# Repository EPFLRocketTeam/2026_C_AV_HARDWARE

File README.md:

# 2026_C_AV_HARDWARE
Repository containing PCBs files of FH2 Avionics

## Guidelines
This repository should be used to share your hardware project files with other members of the team.
Add your project root folder to the indexing and create commits with tags to track versioning of your PCB as you make progress in the design.
Create a tagged release for each major version of your PCB that enters production.
As the repository holds all the AV boards CAD files, you should prefix the tag with the name of your subfolder project.
Take care to preserve tags and respective folders of other members.

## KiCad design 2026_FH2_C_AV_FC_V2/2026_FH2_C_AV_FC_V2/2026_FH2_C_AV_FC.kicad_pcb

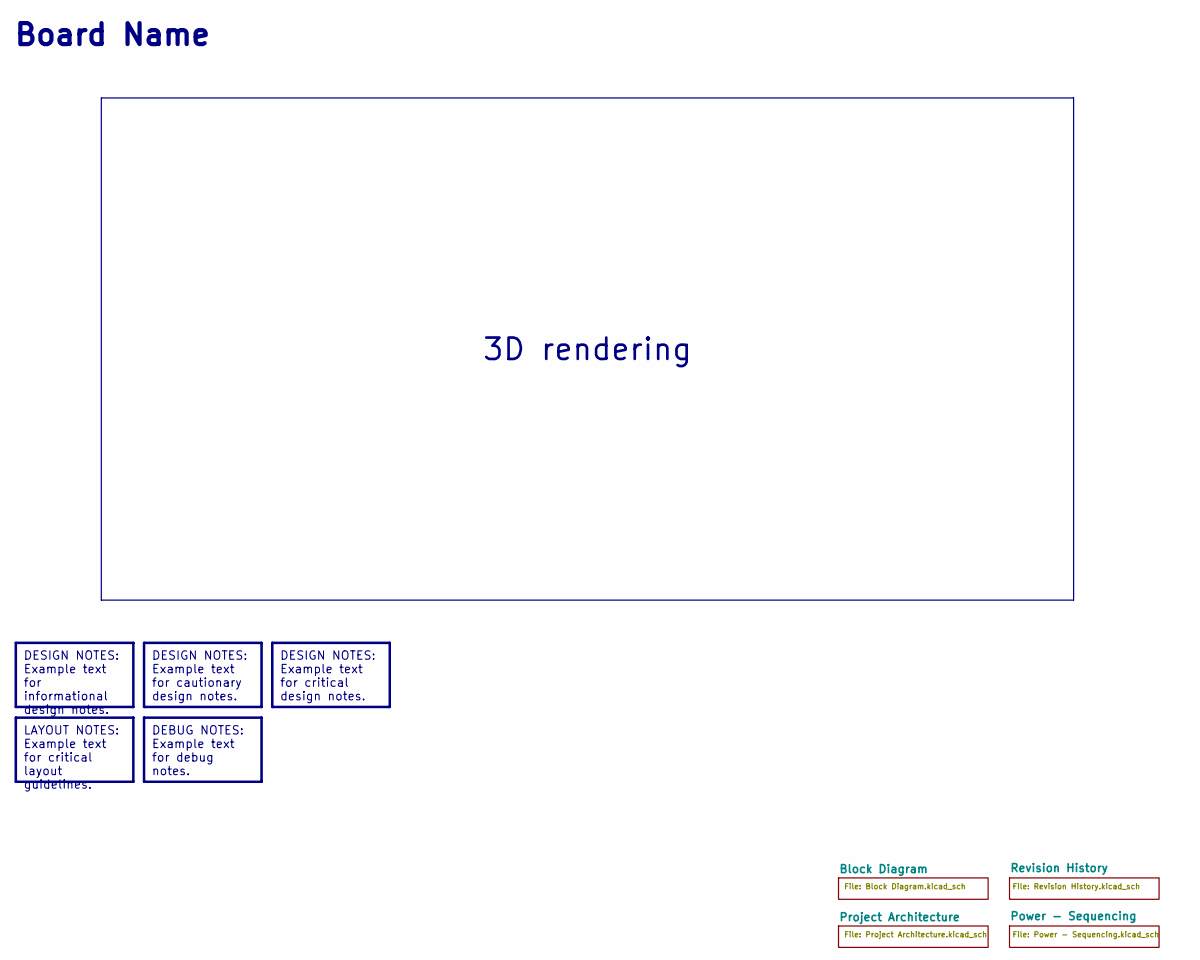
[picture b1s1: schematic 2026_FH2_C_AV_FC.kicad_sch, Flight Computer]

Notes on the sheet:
Board Name
DESIGN NOTES: Example text for informational design notes.
3D rendering
DESIGN NOTES: Example text for critical design notes.
DESIGN NOTES: Example text for cautionary design notes.
DEBUG NOTES: Example text for debug notes.
LAYOUT NOTES: Example text for critical layout guidelines.

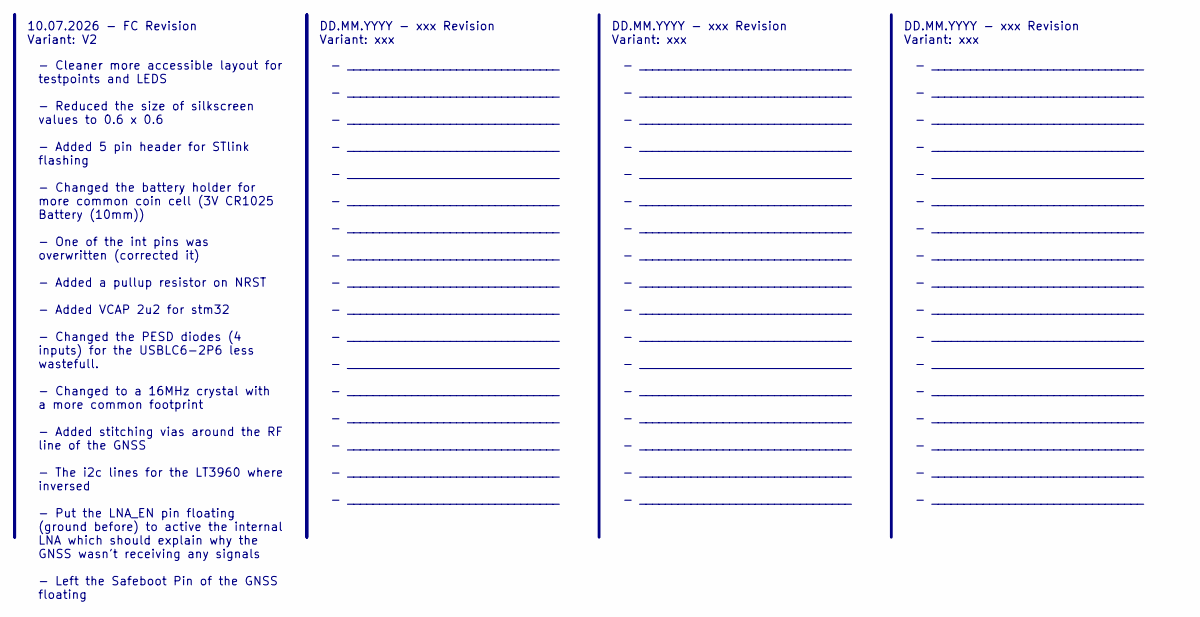
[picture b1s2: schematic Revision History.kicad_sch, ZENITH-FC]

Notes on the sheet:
- _________________________________ - _________________________________ - _________________________________ - _________________________________ - _________________________________ - _________________________________ - _________________________________ - _________________________________ - _________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
DD.MM.YYYY - xxx Revision Variant: xxx
- Cleaner more accessible layout for testpoints and LEDS - Reduced the size of silkscreen values to 0.6 x 0.6 - Added 5 pin header for STlink flashing - Changed the battery holder for more common coin cell (3V CR1025 Battery (10mm)) - One of the int pins was overwritten (corrected it) - Added a pul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
10.07.2026 - FC Revision Variant: V2

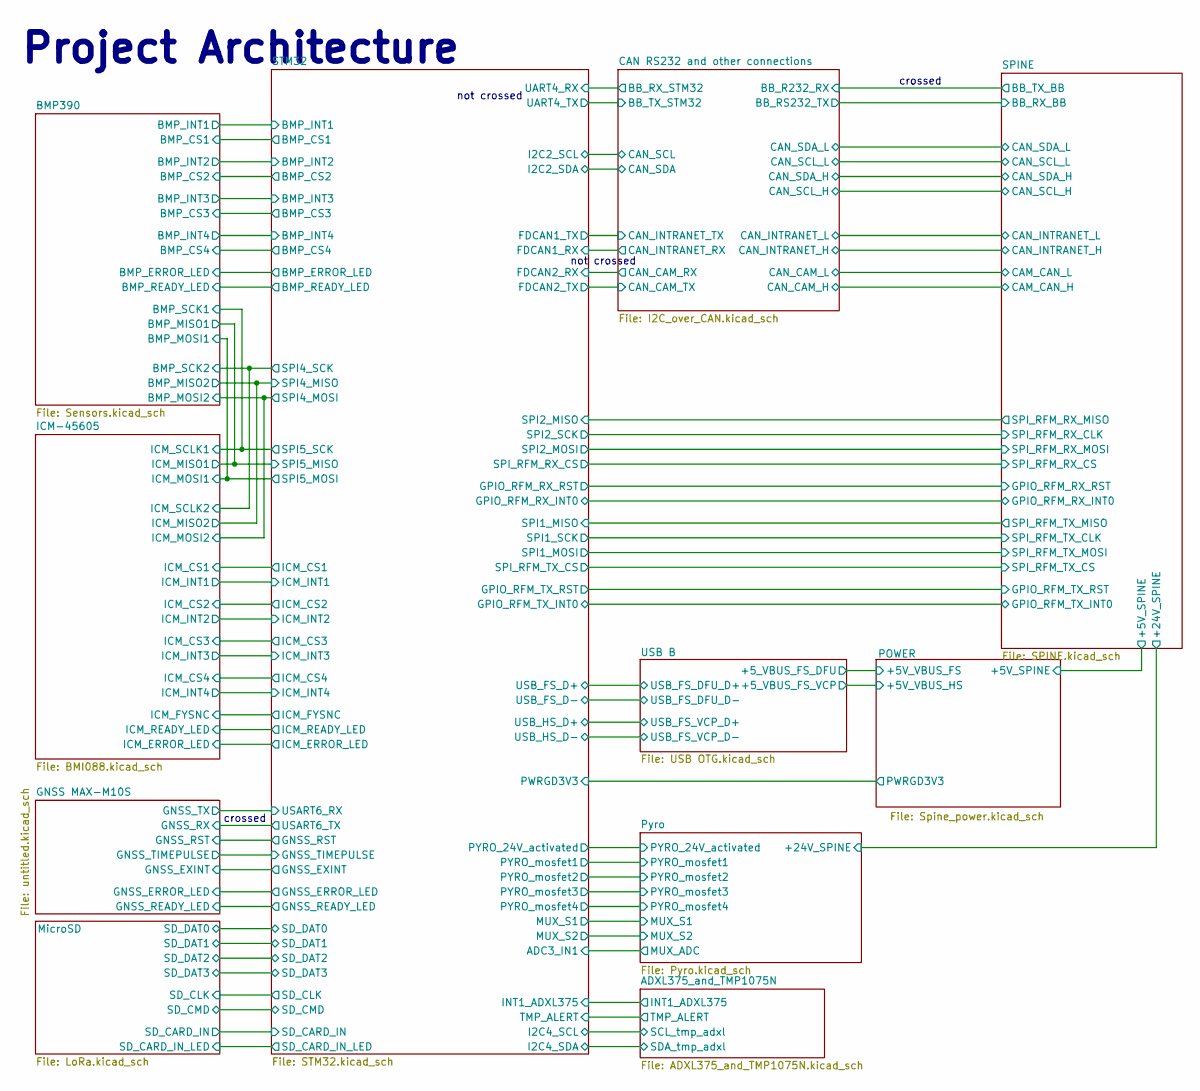
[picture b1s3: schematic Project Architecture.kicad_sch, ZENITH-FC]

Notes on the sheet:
Project Architecture
not crossed
crossed

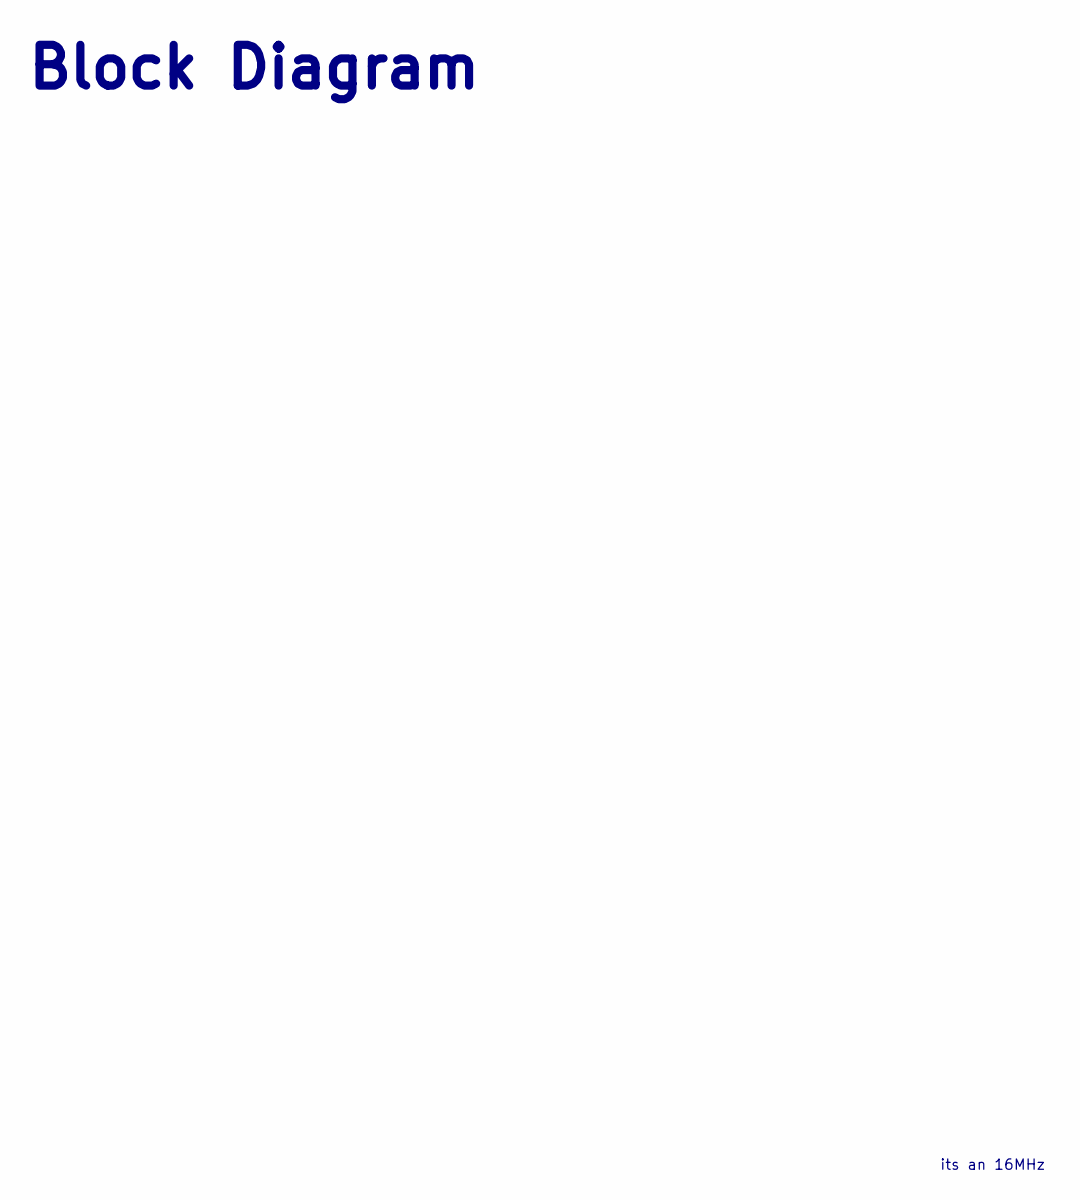
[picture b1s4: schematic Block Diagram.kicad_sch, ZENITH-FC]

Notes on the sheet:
its an 16MHz
Block Diagram

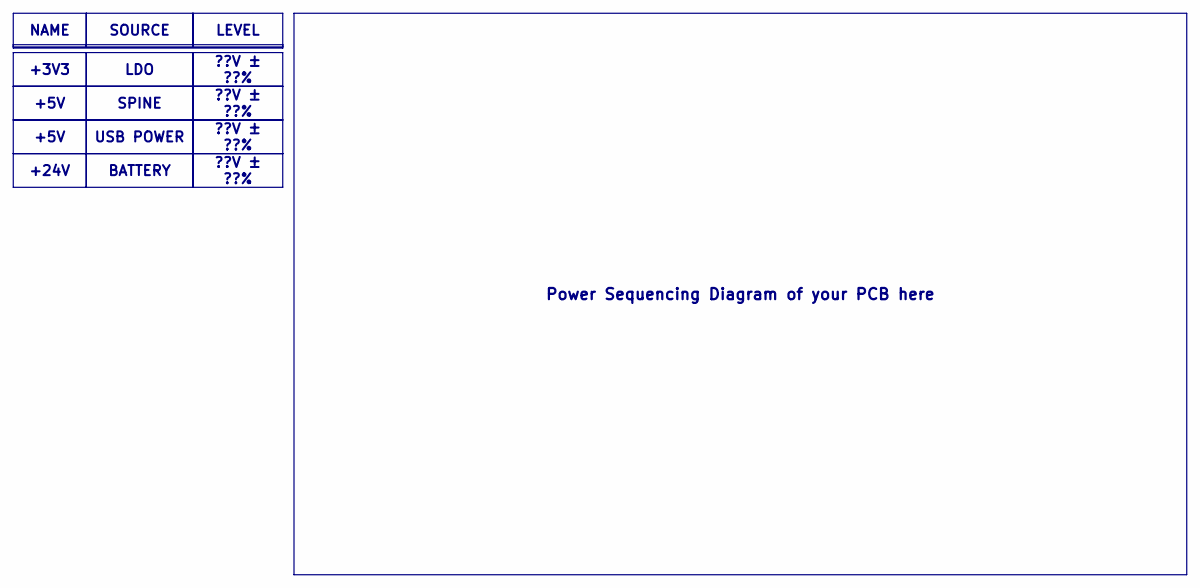
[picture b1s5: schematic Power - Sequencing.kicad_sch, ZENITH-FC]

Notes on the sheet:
+5V
??V ± ??%
SOURCE
BATTERY
SPINE
+24V
USB POWER
LDO
Power Sequencing Diagram of your PCB here
LEVEL
+3V3
NAME

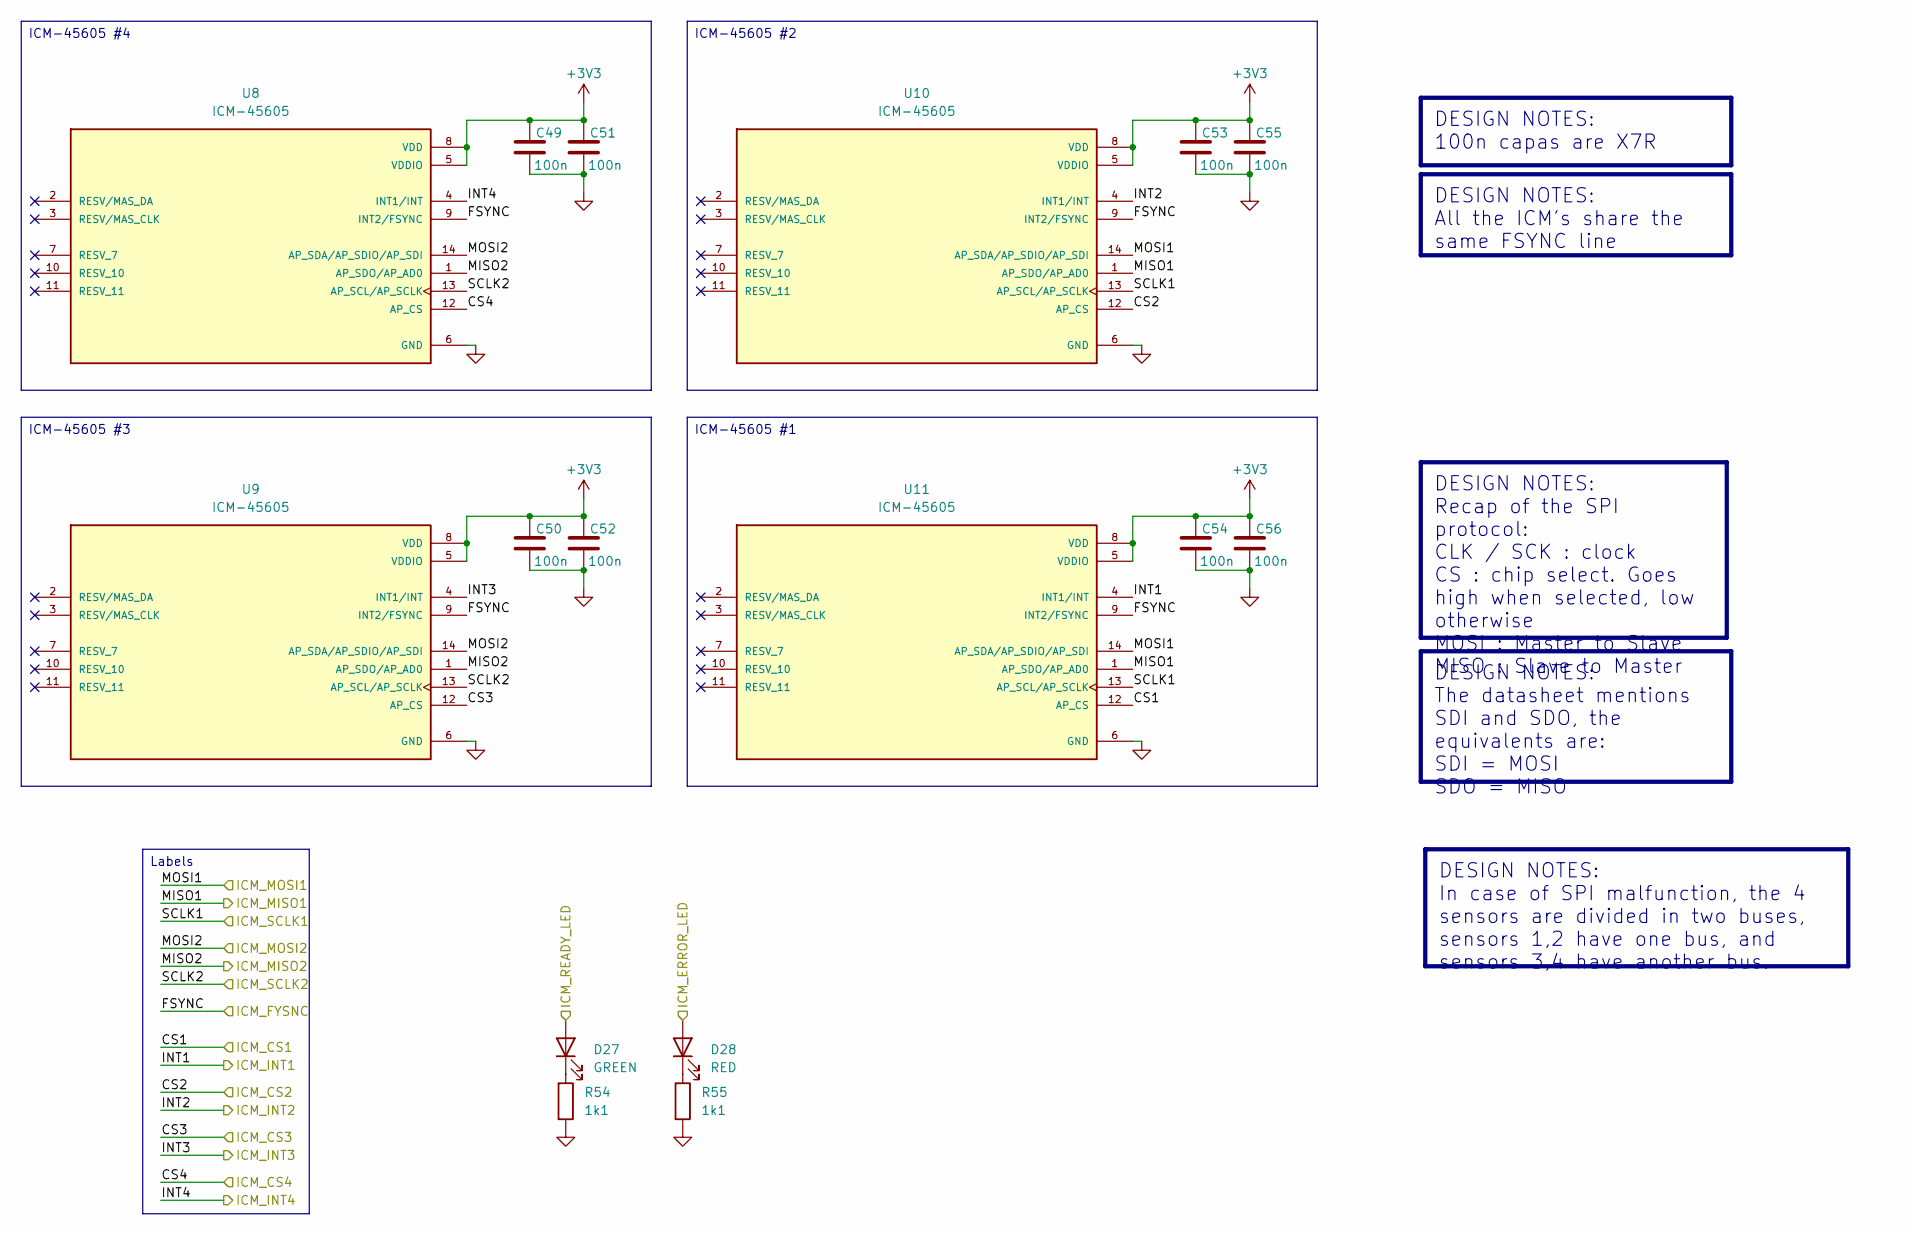
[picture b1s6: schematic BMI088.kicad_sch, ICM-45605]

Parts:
C49, C50, C51, C52, C53, C54, C55, C56: 100n; C_0603_1608Metric; Mouser Part Number 581-06035C104JAT2A
D27: GREEN; LED_0603_1608Metric
D28: RED; LED_0603_1608Metric
R54, R55: 1k1; R_0603_1608Metric; Mouser Part Number 603-RT0603FRE071K1L
U8, U9, U10, U11: ICM-45605; XDCR_ICM-45605; PARTREV 1.0; Mouser Part Number 410-ICM-45605

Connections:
+3V3: C49.2, C50.2, C51.2, C52.2, C53.2, C54.2, C55.2, C56.2, U8.5 (VDDIO), U8.8 (VDD), U9.5 (VDDIO), U9.8 (VDD), U10.5 (VDDIO), U10.8 (VDD), U11.5 (VDDIO), U11.8 (VDD); also elsewhere on the board
/Project Architecture/BMP390/MISO1: U10.1 (AP_SDO/AP_AD0), U11.1 (AP_SDO/AP_AD0); also elsewhere on the board
/Project Architecture/BMP390/MISO2: U8.1 (AP_SDO/AP_AD0), U9.1 (AP_SDO/AP_AD0); also elsewhere on the board
/Project Architecture/BMP390/MOSI1: U10.14 (AP_SDA/AP_SDIO/AP_SDI), U11.14 (AP_SDA/AP_SDIO/AP_SDI); also elsewhere on the board
/Project Architecture/BMP390/MOSI2: U8.14 (AP_SDA/AP_SDIO/AP_SDI), U9.14 (AP_SDA/AP_SDIO/AP_SDI); also elsewhere on the board
/Project Architecture/BMP390/SCK1: U10.13 (AP_SCL/AP_SCLK), U11.13 (AP_SCL/AP_SCLK); also elsewhere on the board
/Project Architecture/BMP390/SCK2: U8.13 (AP_SCL/AP_SCLK), U9.13 (AP_SCL/AP_SCLK); also elsewhere on the board
/Project Architecture/ICM-45605/CS1: U11.12 (AP_CS); also elsewhere on the board
/Project Architecture/ICM-45605/CS2: U10.12 (AP_CS); also elsewhere on the board
/Project Architecture/ICM-45605/CS3: U9.12 (AP_CS); also elsewhere on the board
/Project Architecture/ICM-45605/CS4: U8.12 (AP_CS); also elsewhere on the board
/Project Architecture/ICM-45605/FSYNC: U8.9 (INT2/FSYNC), U9.9 (INT2/FSYNC), U10.9 (INT2/FSYNC), U11.9 (INT2/FSYNC); also elsewhere on the board
/Project Architecture/ICM-45605/ICM_ERROR_LED: D28.2 (A); also elsewhere on the board
/Project Architecture/ICM-45605/ICM_READY_LED: D27.2 (A); also elsewhere on the board
/Project Architecture/ICM-45605/INT1: U11.4 (INT1/INT); also elsewhere on the board
/Project Architecture/ICM-45605/INT2: U10.4 (INT1/INT); also elsewhere on the board
/Project Architecture/ICM-45605/INT3: U9.4 (INT1/INT); also elsewhere on the board
/Project Architecture/ICM-45605/INT4: U8.4 (INT1/INT); also elsewhere on the board
GND: C49.1, C50.1, C51.1, C52.1, C53.1, C54.1, C55.1, C56.1, R54.2, R55.2, U8.6 (GND), U9.6 (GND), U10.6 (GND), U11.6 (GND); also elsewhere on the board
unnamed: D27.1 (K), R54.1
unnamed: D28.1 (K), R55.1

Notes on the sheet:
DESIGN NOTES: Recap of the SPI protocol: CLK / SCK : clock CS : chip select. Goes high when selected, low otherwise MOSI : Master to Slave MISO : Slave to Master
Labels
DESIGN NOTES: 100n capas are X7R
ICM-45605 #4
ICM-45605 #2
DESIGN NOTES: The datasheet mentions SDI and SDO, the equivalents are: SDI = MOSI SDO = MISO
DESIGN NOTES: All the ICM's share the same FSYNC line
DESIGN NOTES: In case of SPI malfunction, the 4 sensors are divided in two buses, sensors 1,2 have one bus, and sensors 3,4 have another bus.
ICM-45605 #1
ICM-45605 #3

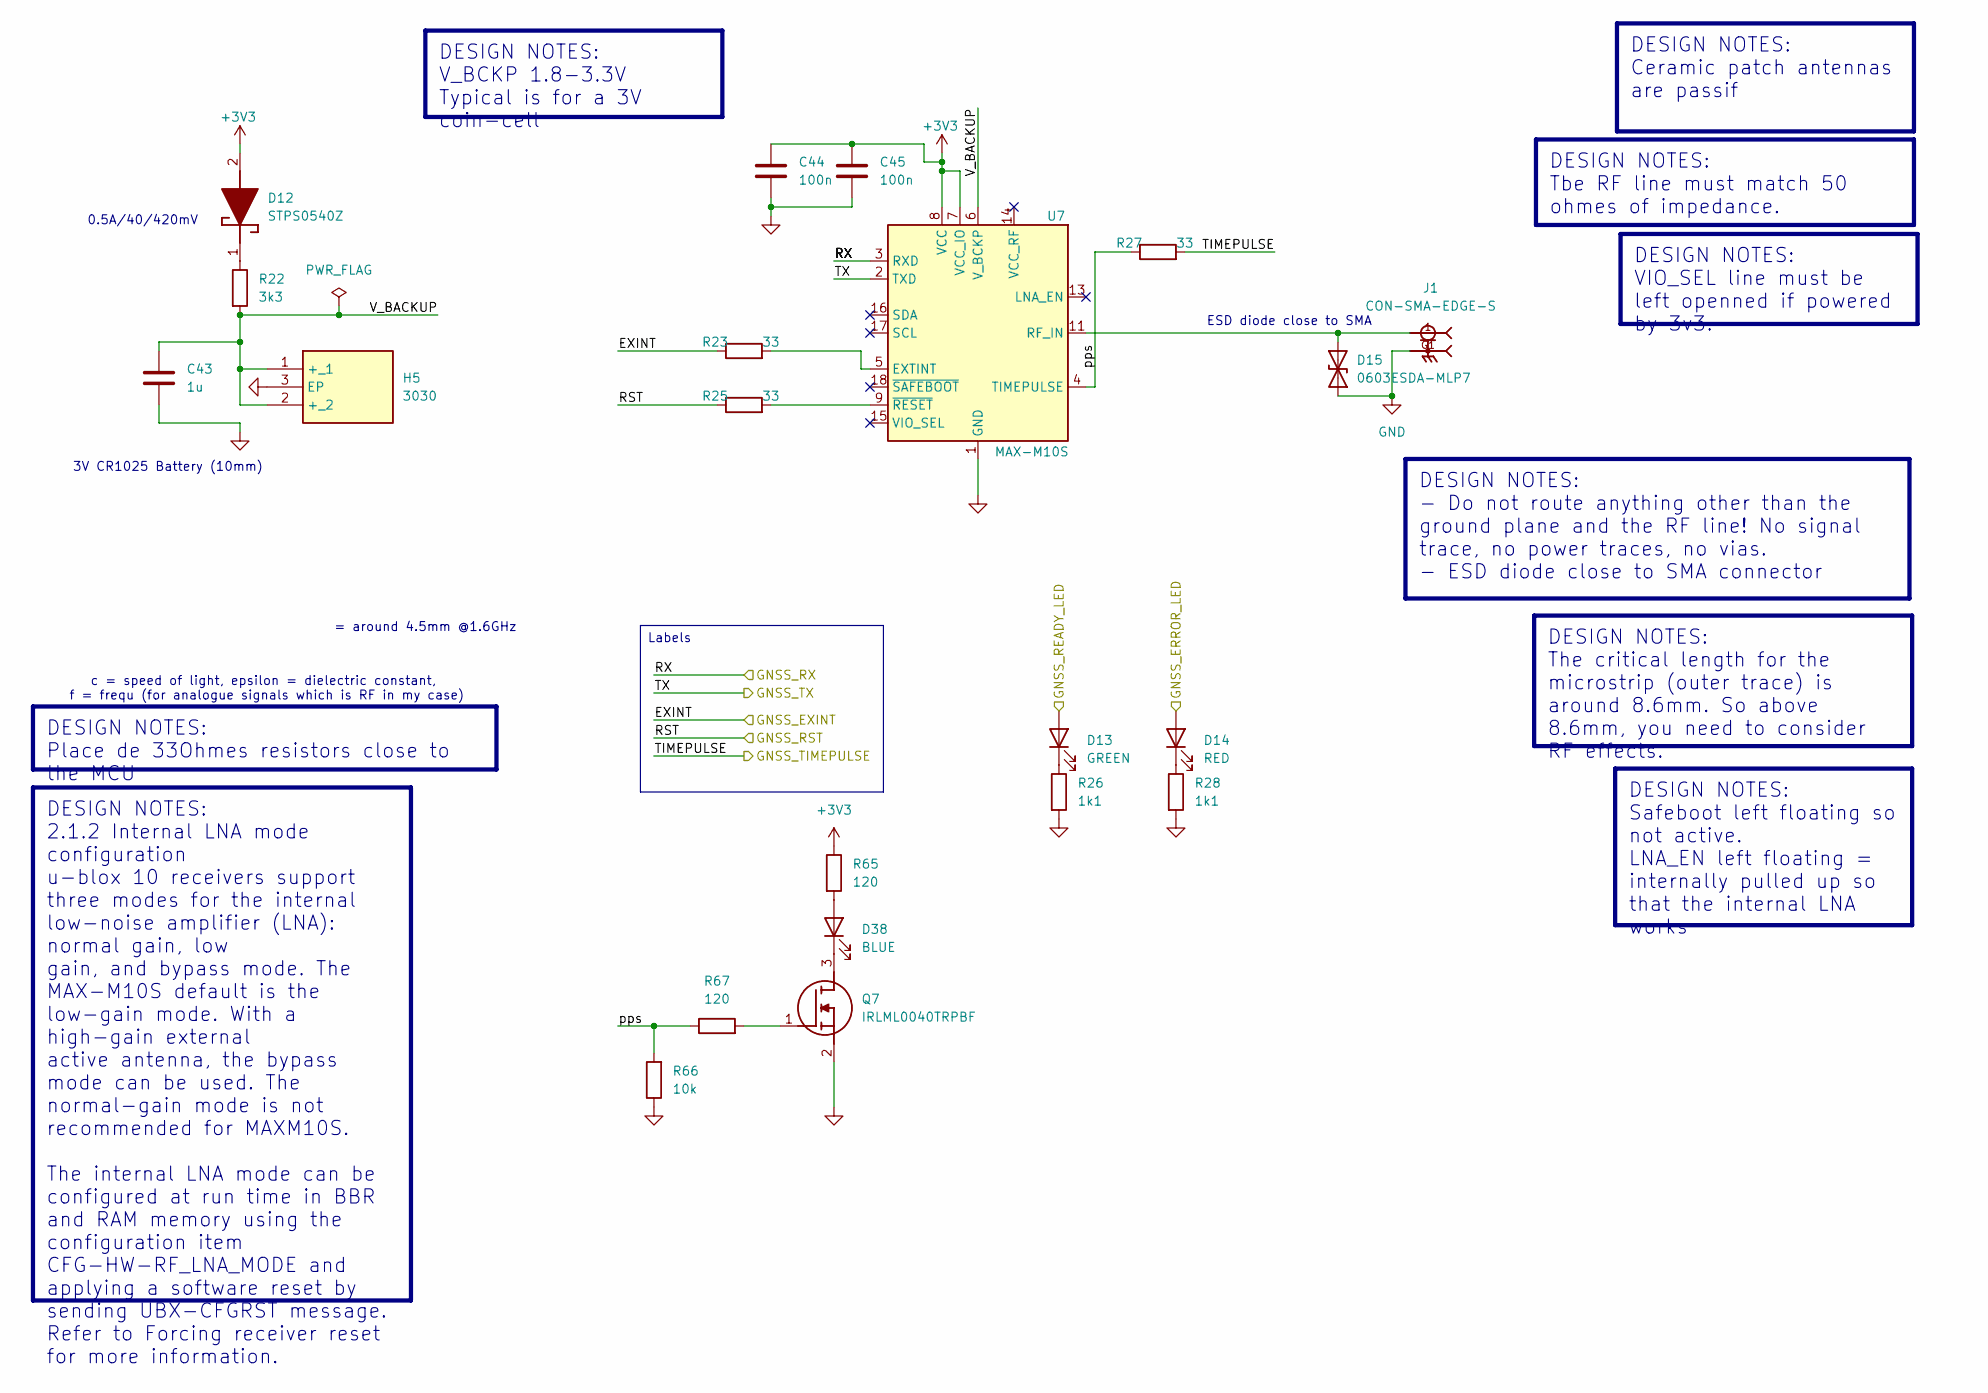
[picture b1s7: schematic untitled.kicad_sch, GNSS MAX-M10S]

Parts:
C43: 1u; C_0603_1608Metric; Mouser Part Number 581-0603YD105KAT4A
C44, C45: 100n; C_0603_1608Metric; Mouser Part Number 581-06035C104JAT2A
D12: STPS0540Z; Mouser Part Number 511-STPS0540Z
D13: GREEN; LED_0603_1608Metric
D14: RED; LED_0603_1608Metric
D15: 0603ESDA-MLP7; D_0603_1608Metric; Mouser Part Number 504-0603ESDA-MLP7
D38: BLUE; LED_0603_1608Metric
H5: 3030; Mouser Part Number 534-3030
J1: CON-SMA-EDGE-S; RFSOLUTIONS_CON-SMA-EDGE-S; PARTREV 1
Q7: IRLML0040TRPBF; SOT95P237X112-3N; Mouser Part Number 942-IRLML0040TRPBF
R22: 3k3; R_0603_1608Metric; Mouser Part Number 603-RC0603FR-133K3L
R23, R25, R27: 33; R_0402_1005Metric; Mouser Part Number 603-RC0402FR-7D33RL
R26, R28: 1k1; R_0603_1608Metric; Mouser Part Number 603-RT0603FRE071K1L
R65, R67: 120; R_0603_1608Metric; Mouser Part Number 603-RC0603FR-13120RL
R66: 10k; R_0603_1608Metric; Mouser Part Number 603-AC0603FRE0710KL
U7: MAX-M10S; ublox_MAX; Mouser Part Number 377-MAX-M10S-00B

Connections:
+3V3: C44.1, C45.1, D12.2 (A), R65.1, U7.7 (VCC_IO), U7.8 (VCC); also elsewhere on the board
/Project Architecture/GNSS MAX-M10S/EXINT: R23.1; also elsewhere on the board
/Project Architecture/GNSS MAX-M10S/GNSS_ERROR_LED: D14.2 (A); also elsewhere on the board
/Project Architecture/GNSS MAX-M10S/GNSS_READY_LED: D13.2 (A); also elsewhere on the board
/Project Architecture/GNSS MAX-M10S/RST: R25.1; also elsewhere on the board
/Project Architecture/GNSS MAX-M10S/RX: U7.3 (RXD); also elsewhere on the board
/Project Architecture/GNSS MAX-M10S/TIMEPULSE: R27.2; also elsewhere on the board
/Project Architecture/GNSS MAX-M10S/TX: U7.2 (TXD); also elsewhere on the board
/Project Architecture/GNSS MAX-M10S/V_BACKUP: C43.1, H5.1 (+_1), H5.2 (+_2), R22.2, U7.6 (V_BCKP)
/Project Architecture/GNSS MAX-M10S/pps: R27.1, R66.2, R67.1, U7.4 (TIMEPULSE)
GND: C43.2, C44.2, C45.2, D15.1 (A1), H5.3 (EP), J1.G1, J1.G2, J1.G3, J1.G4, Q7.2 (S), R26.2, R28.2, R66.1, U7.1 (GND), U7.10 (GND), U7.12 (GND); also elsewhere on the board
unnamed: D12.1 (K), R22.1
unnamed: D13.1 (K), R26.1
unnamed: D14.1 (K), R28.1
unnamed: D15.2 (A2), J1.1, U7.11 (RF_IN)
unnamed: D38.2 (A), R65.2
unnamed: D38.1 (K), Q7.3 (D)
unnamed: Q7.1 (G), R67.2
unnamed: R23.2, U7.5 (EXTINT)
unnamed: R25.2, U7.9 (~RESET)

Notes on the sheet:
3V CR1025 Battery (10mm)
ESD diode close to SMA
= around 4.5mm @1.6GHz
0.5A/40/420mV
c = speed of light, epsilon = dielectric constant, f = frequ (for analogue signals which is RF in my case)
DESIGN NOTES: Place de 33Ohmes resistors close to the MCU
DESIGN NOTES: VIO_SEL line must be left openned if powered by 3v3.
DESIGN NOTES: - Do not route anything other than the ground plane and the RF line! No signal trace, no power traces, no vias. - ESD diode close to SMA connector
DESIGN NOTES: Tbe RF line must match 50 ohmes of impedance.
DESIGN NOTES: V_BCKP 1.8-3.3V Typical is for a 3V coin-cell
DESIGN NOTES: 2.1.2 Internal LNA mode configuration u-blox 10 receivers support three modes for the internal low-noise amplifier (LNA): normal gain, low gain, and bypass mode. The MAX-M10S default is the low-gain mode. With a high-gain external active antenna, the bypass mode can be used. The norma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
DESIGN NOTES: Safeboot left floating so not active. LNA_EN left floating = internally pulled up so that the internal LNA works
DESIGN NOTES: Ceramic patch antennas are passif
DESIGN NOTES: The critical length for the microstrip (outer trace) is around 8.6mm. So above 8.6mm, you need to consider RF effects.
Labels

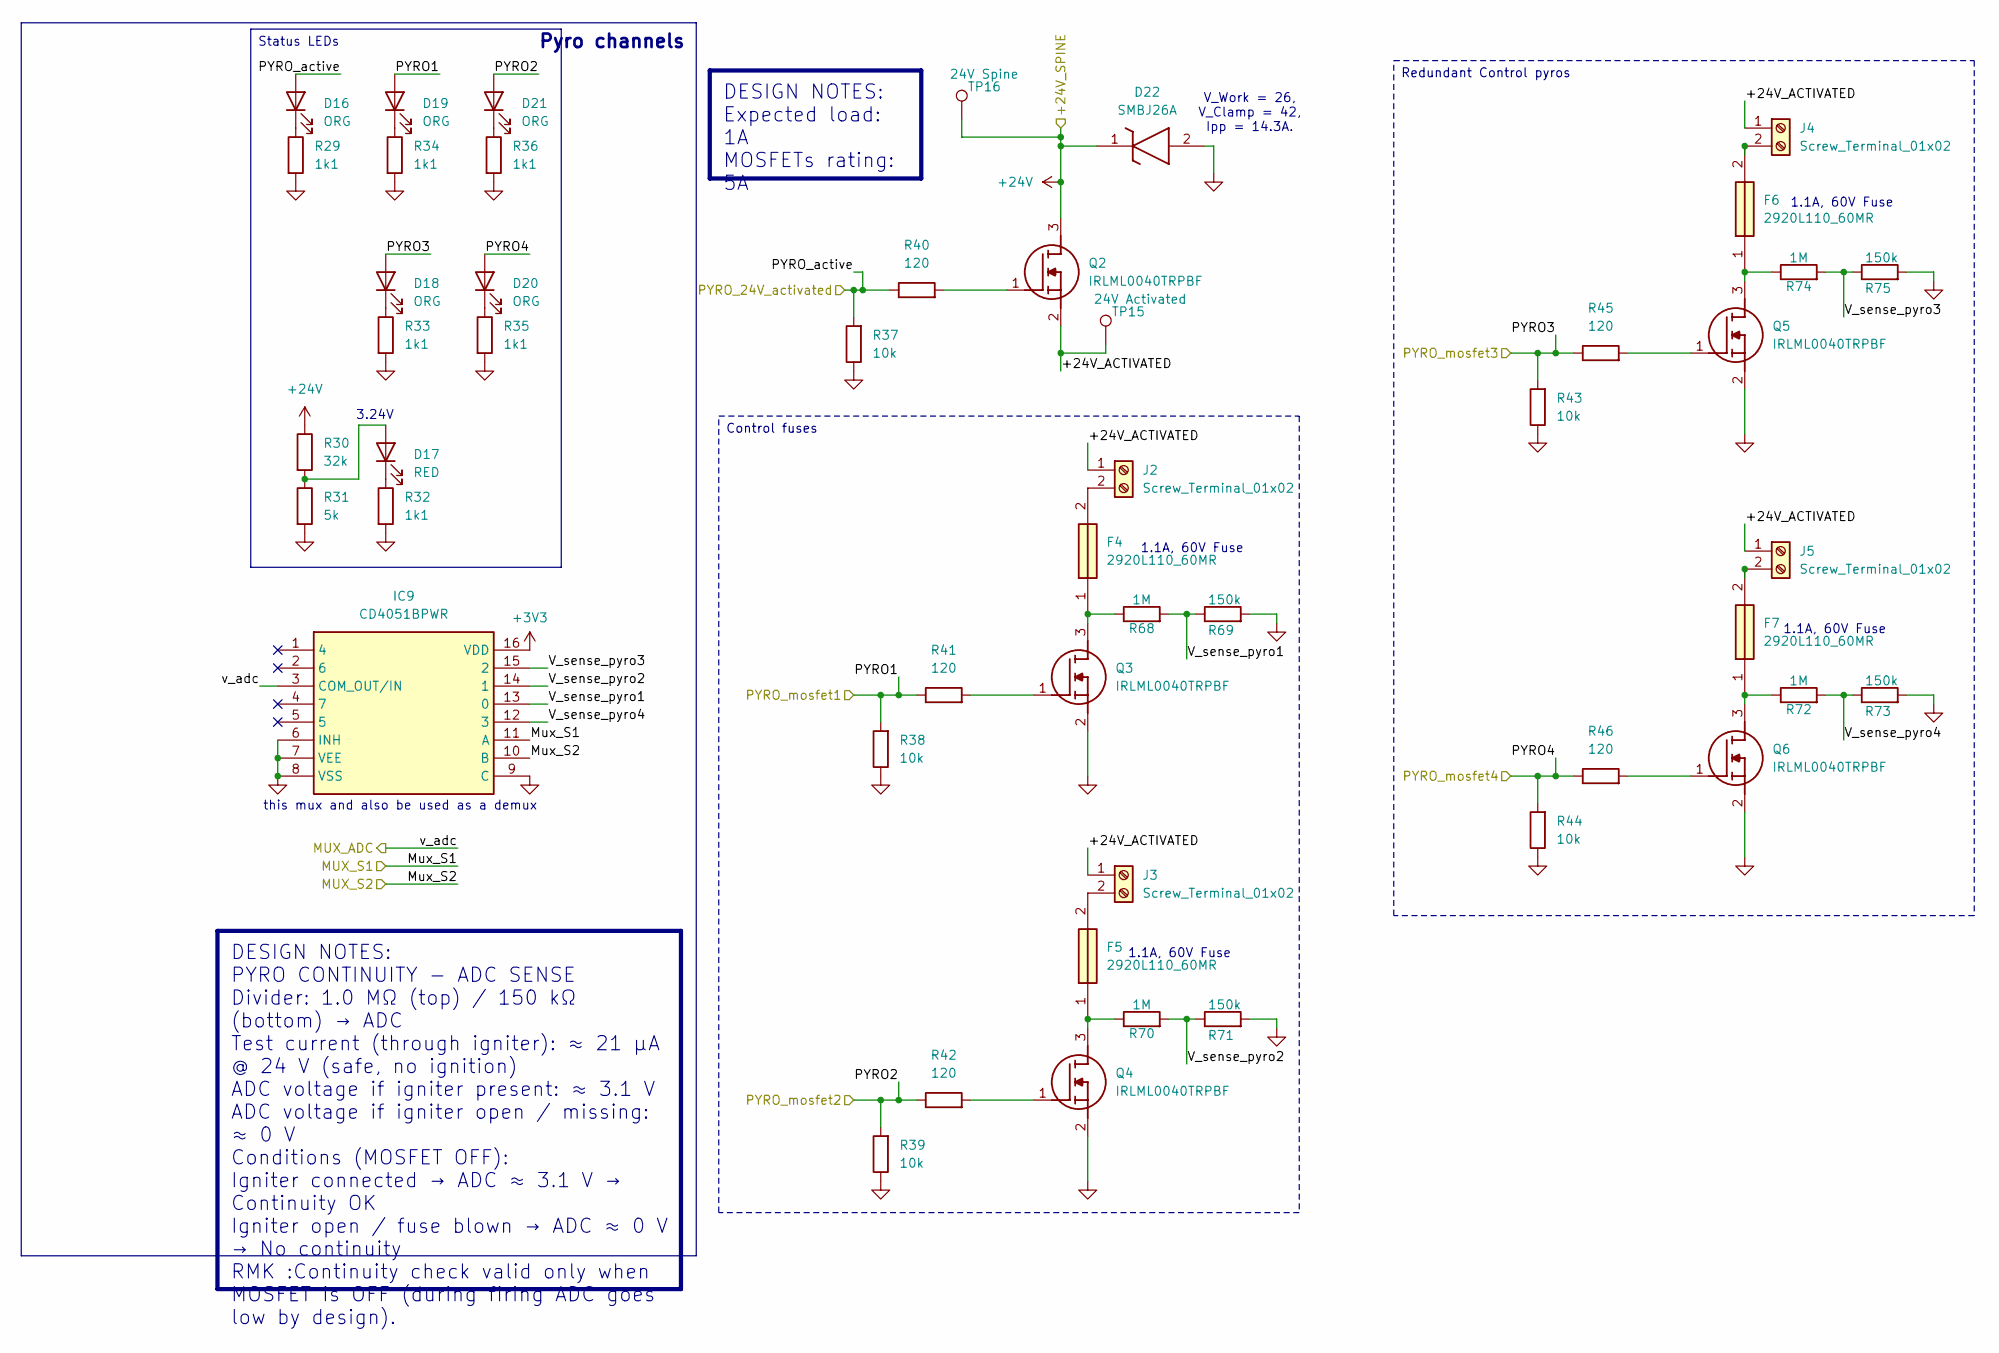
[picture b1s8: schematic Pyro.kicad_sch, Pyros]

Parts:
D16, D18, D19, D20, D21: ORG; LED_0603_1608Metric
D17: RED; LED_0603_1608Metric
D22: SMBJ26A; DIOM5436X261N; Mouser Part Number 576-SMBJ26A
F4, F5, F6, F7: 2920L110_60MR; 2920L07560MR; Mouser Part Number 576-2920L110/60MR
IC9: CD4051BPWR; TSSOP-16_4.4x5mm_P0.65mm; Mouser Part Number 595-CD4051BPWR
J2, J3, J4, J5: Screw_Terminal_01x02; 395434302
Q2, Q3, Q4, Q5, Q6: IRLML0040TRPBF; SOT95P237X112-3N; Mouser Part Number 942-IRLML0040TRPBF
R29, R32, R33, R34, R35, R36: 1k1; R_0603_1608Metric; Mouser Part Number 603-RT0603FRE071K1L
R30: 32k; R_0603_1608Metric; Mouser Part Number 603-RC0603FR-0732K4L
R31: 5k; R_0603_1608Metric; Mouser Part Number 603-AF0603DR-074K99L
R37, R38, R39, R43, R44: 10k; R_0603_1608Metric; Mouser Part Number 603-AC0603FRE0710KL
R40, R41, R42, R45, R46: 120; R_0603_1608Metric; Mouser Part Number 603-RC0603FR-13120RL
R68, R70, R72, R74: 1M; R_0603_1608Metric; Mouser Part Number 603-RC0603FR-071MP
R69, R71, R73, R75: 150k; R_0603_1608Metric; Mouser Part Number 603-RE0603FRE07150KL
TP15: 24V Activated; TestPoint_THTPad_1.0x1.0mm_Drill0.5mm
TP16: 24V Spine; TestPoint_THTPad_1.0x1.0mm_Drill0.5mm

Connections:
+3V3: IC9.16 (VDD); also elsewhere on the board
+24V: D22.1 (K), Q2.3 (D), R30.1, TP16.1; also elsewhere on the board
/Project Architecture/Pyro/+24V_ACTIVATED: J2.1, J3.1, J4.1, J5.1, Q2.2 (S), TP15.1
/Project Architecture/Pyro/Mux_S1: IC9.11 (A); also elsewhere on the board
/Project Architecture/Pyro/Mux_S2: IC9.10 (B); also elsewhere on the board
/Project Architecture/Pyro/PYRO1: D19.2 (A), R38.2, R41.1; also elsewhere on the board
/Project Architecture/Pyro/PYRO2: D21.2 (A), R39.2, R42.1; also elsewhere on the board
/Project Architecture/Pyro/PYRO3: D18.2 (A), R43.2, R45.1; also elsewhere on the board
/Project Architecture/Pyro/PYRO4: D20.2 (A), R44.2, R46.1; also elsewhere on the board
/Project Architecture/Pyro/PYRO_active: D16.2 (A), R37.2, R40.1; also elsewhere on the board
/Project Architecture/Pyro/V_sense_pyro1: IC9.13 (0), R68.2, R69.1
/Project Architecture/Pyro/V_sense_pyro2: IC9.14 (1), R70.2, R71.1
/Project Architecture/Pyro/V_sense_pyro3: IC9.15 (2), R74.2, R75.1
/Project Architecture/Pyro/V_sense_pyro4: IC9.12 (3), R72.2, R73.1
/Project Architecture/Pyro/v_adc: IC9.3 (COM_OUT/IN); also elsewhere on the board
GND: D22.2 (A), IC9.6 (INH), IC9.7 (VEE), IC9.8 (VSS), IC9.9 (C), Q3.2 (S), Q4.2 (S), Q5.2 (S), Q6.2 (S), R29.2, R31.2, R32.2, R33.2, R34.2, R35.2, R36.2, R37.1, R38.1, R39.1, R43.1, R44.1, R69.2, R71.2, R73.2, R75.2; also elsewhere on the board
unnamed: D16.1 (K), R29.1
unnamed: D17.2 (A), R30.2, R31.1
unnamed: D17.1 (K), R32.1
unnamed: D18.1 (K), R33.1
unnamed: D19.1 (K), R34.1
unnamed: D20.1 (K), R35.1
unnamed: D21.1 (K), R36.1
unnamed: F4.2, J2.2
unnamed: F5.2, J3.2
unnamed: F6.2, J4.2
unnamed: F7.2, J5.2
unnamed: Q2.1 (G), R40.2
unnamed: F4.1, Q3.3 (D), R68.1
unnamed: Q3.1 (G), R41.2
unnamed: F5.1, Q4.3 (D), R70.1
unnamed: Q4.1 (G), R42.2
unnamed: F6.1, Q5.3 (D), R74.1
unnamed: Q5.1 (G), R45.2
unnamed: F7.1, Q6.3 (D), R72.1
unnamed: Q6.1 (G), R46.2

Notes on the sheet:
3.24V
1.1A, 60V Fuse
this mux and also be used as a demux
V_Work = 26, V_Clamp = 42, Ipp = 14.3A.
Status LEDs
DESIGN NOTES: PYRO CONTINUITY - ADC SENSE Divider: 1.0 MΩ (top) / 150 kΩ (bottom) → ADC Test current (through igniter): ≈ 21 µA @ 24 V (safe, no ignition) ADC voltage if igniter present: ≈ 3.1 V ADC voltage if igniter open / missing: ≈ 0 V Conditions (MOSFET OFF): Igniter connected → ADC ≈ 3.1 V → 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
Pyro channels
Redundant Control pyros
Control fuses
DESIGN NOTES: Expected load: 1A MOSFETs rating: 5A

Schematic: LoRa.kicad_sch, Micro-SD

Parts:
C47: 1u; C_0603_1608Metric; Mouser Part Number 581-0603YD105KAT4A
C48: 100n; C_0603_1608Metric; Mouser Part Number 581-06035C104JAT2A
D23, D24: PESD4USB3UTBS; PESD4USB3UTBSQX; Mouser Part Number 771-PESD4USB3UTBS-QX
D26: YELLOW; LED_0603_1608Metric
J6: Micro_SD_Card_Det_Hirose_DM3AT; microSD_HC_Hirose_DM3AT-SF-PEJM5; Mouser Part Number 798-DM3AT-SF-PEJM5
R47, R48, R49, R50, R51, R52: 33; R_0402_1005Metric; Mouser Part Number 603-RC0402FR-7D33RL
R53: 1k1; R_0603_1608Metric; Mouser Part Number 603-RT0603FRE071K1L

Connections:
+3V3: C47.1, C48.1, D24.5, D24.6, J6.4 (VDD); also elsewhere on the board
/Project Architecture/MicroSD/SD_CARD_IN: J6.10 (DET_A); also elsewhere on the board
/Project Architecture/MicroSD/SD_CARD_IN_LED: D26.2 (A); also elsewhere on the board
/Project Architecture/MicroSD/SD_CLK: R52.1; also elsewhere on the board
/Project Architecture/MicroSD/SD_CMD: R51.1; also elsewhere on the board
/Project Architecture/MicroSD/SD_DAT0: R47.1; also elsewhere on the board
/Project Architecture/MicroSD/SD_DAT1: R48.1; also elsewhere on the board
/Project Architecture/MicroSD/SD_DAT2: R49.1; also elsewhere on the board
/Project Architecture/MicroSD/SD_DAT3: R50.1; also elsewhere on the board
/Project Architecture/MicroSD/clk: D23.4, D23.7, J6.5 (CLK), R52.2
/Project Architecture/MicroSD/cmd: D24.1, D24.10, J6.3 (CMD), R51.2
/Project Architecture/MicroSD/dat0: D23.2, D23.9, J6.7 (DAT0), R47.2
/Project Architecture/MicroSD/dat1: D23.1, D23.10, J6.8 (DAT1), R48.2
/Project Architecture/MicroSD/dat2: D24.4, D24.7, J6.1 (DAT2), R49.2
/Project Architecture/MicroSD/dat3: D24.2, D24.9, J6.2 (DAT3/CD), R50.2
GND: C47.2, C48.2, D23.3, D23.8, D24.3, D24.8, J6.6 (VSS), J6.9 (DET_B), J6.11 (SHIELD), R53.2; also elsewhere on the board
unnamed: D26.1 (K), R53.1

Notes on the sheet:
the order is horrible but it makes it easier for the pcb layout
DESIGN NOTES: DET_A,B = Card detect switch pins. Behaviour: - open circuit when no card - short circuit when card (pulled low) The GPIO must have an internal resistor (~47k). GPIO = HIGH = No card GPIO = LOW = Card
DESIGN NOTES: Pull up internally the GPIOs for the - CMD - D[0,1,2,3] Do not pull up CLK. Leave unpulled in cubeIDE The pins need a pull up resistor of about 10k-100k, the internal pull-ups provide around 40-50k. 47k is a typical value for external pull-ups. -> pullup in cubeIDE
DESIGN NOTES: Add 33Ohme resistors in serie to every logic line, So CMD, D[0,1,2,3] and CLK
DESIGN NOTES: ESD protection: Low capacitance TVS diodes (<5pf), with working voltage V_RWM aroud 5V
DESIGN NOTES: Try to keep DAT[0,1,2,3], CLK and CMD lines around the same lenght. <10mm difference is recommended for a typical application.

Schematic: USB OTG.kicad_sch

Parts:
D4, D7: RED; LED_0603_1608Metric
J9, J10: MUSB-05-S-B-SM-A-K-TR; MUSB05SBSMAKTR; Mouser Part Number 200-MUSB05SBSMAKTR
R5, R78: 1k1; R_0603_1608Metric; Mouser Part Number 603-RT0603FRE071K1L
U17, U19: USBLC6-2P6; SOT-666; Mouser Part Number 511-USBLC6-2P6

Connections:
/Project Architecture/USB B/D1+: U19.4 (I/O2); also elsewhere on the board
/Project Architecture/USB B/D1-: U19.6 (I/O1); also elsewhere on the board
/Project Architecture/USB B/D2+: U17.4 (I/O2); also elsewhere on the board
/Project Architecture/USB B/D2-: U17.6 (I/O1); also elsewhere on the board
/Project Architecture/USB B/VBUS1: D7.2 (A), J9.1, U19.5 (VBUS); also elsewhere on the board
/Project Architecture/USB B/VBUS2: D4.2 (A), J10.1, U17.5 (VBUS); also elsewhere on the board
GND: J9.5, J9.MP1, J9.MP2, J9.MP3, J9.MP4, J10.5, J10.MP1, J10.MP2, J10.MP3, J10.MP4, R5.1, R78.1, U17.2 (GND), U19.2 (GND); also elsewhere on the board
unnamed: D4.1 (K), R78.2
unnamed: D7.1 (K), R5.2
unnamed: J9.2, U19.1 (I/O1)
unnamed: J9.3, U19.3 (I/O2)
unnamed: J10.2, U17.1 (I/O1)
unnamed: J10.3, U17.3 (I/O2)

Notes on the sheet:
gnd
vcc
ID floating = device
USB OTG Basics
no TVS here because its on the POWER sheet
Labels
DESIGN NOTES: Route D+ and D- as 90 ohmes differential pair. And match the length.
DESIGN NOTES: We are using 2 USB communication lines: USB OTG FS (Full-speed) = 12Mbps (internal USB PHY in STM32) USB OTG HG (High-speed) = 480Mbps (needs an external USB PHY) DFU_USB-A (Bootloader port) → OTG_USB_FS VCP_USB-A (Virtual COM port) → OTG_USB_HS We will actually be using normal USB an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
USB B Female connector : USB FS VCP
